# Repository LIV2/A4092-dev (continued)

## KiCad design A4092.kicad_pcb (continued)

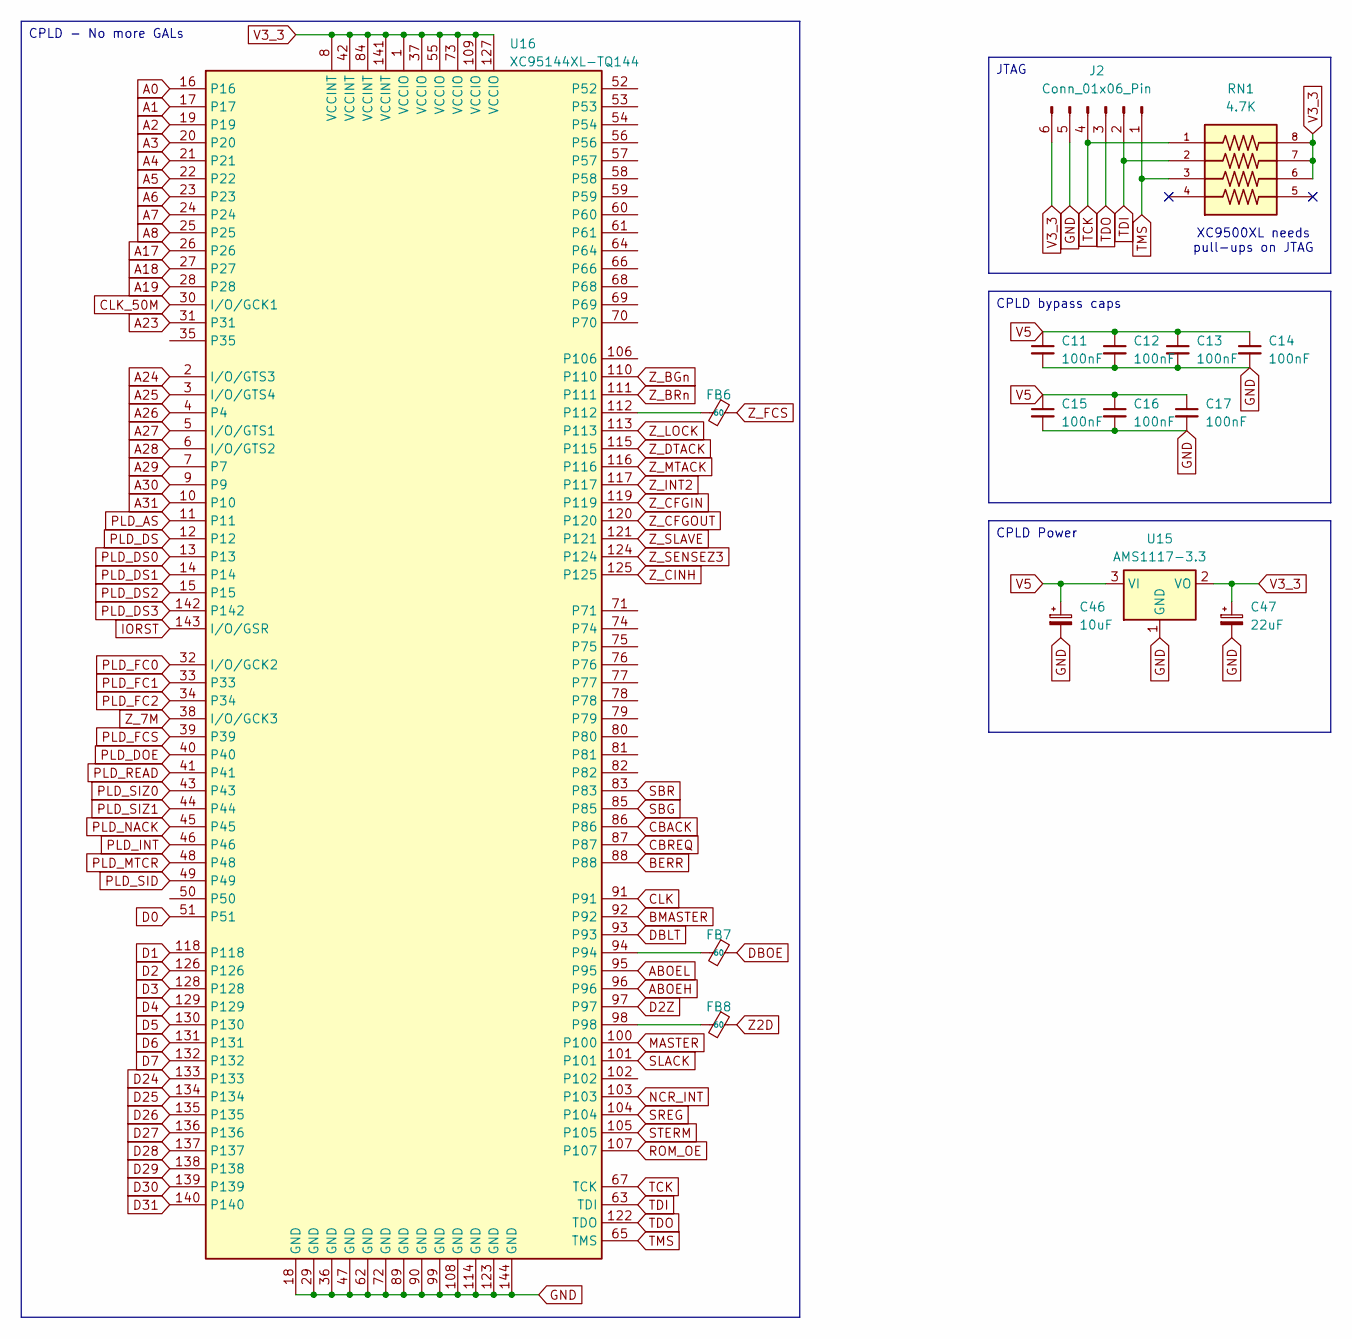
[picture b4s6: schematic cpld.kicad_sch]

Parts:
C11, C12, C13, C14, C15, C16, C17: 100nF; C_0603_1608Metric_Pad1.08x0.95mm_HandSolder
C46: 10uF; CP_Elec_6.3x7.7
C47: 22uF; CP_Elec_6.3x7.7
FB6, FB7, FB8: 60; C_0603_1608Metric_Pad1.08x0.95mm_HandSolder
J2: Conn_01x06_Pin; PinHeader_1x06_P2.54mm_Vertical
RN1: 4.7K; RESCAXS127P508X320X70-8N; PARTREV V.9
U15: AMS1117-3.3; SOT-223-3_TabPin2
U16: XC95144XL-TQ144; 144-TQFP_XIL

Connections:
A0: U16.16; also elsewhere on the board
A1: U16.17; also elsewhere on the board
A2: U16.19; also elsewhere on the board
A3: U16.20; also elsewhere on the board
A4: U16.21; also elsewhere on the board
A5: U16.22; also elsewhere on the board
A6: U16.23; also elsewhere on the board
A7: U16.24; also elsewhere on the board
A8: U16.25; also elsewhere on the board
A17: U16.26; also elsewhere on the board
A18: U16.27; also elsewhere on the board
A19: U16.28; also elsewhere on the board
A23: U16.31; also elsewhere on the board
A24: U16.2 (I/O/GTS3); also elsewhere on the board
A25: U16.3 (I/O/GTS4); also elsewhere on the board
A26: U16.4; also elsewhere on the board
A27: U16.5 (I/O/GTS1); also elsewhere on the board
A28: U16.6 (I/O/GTS2); also elsewhere on the board
A29: U16.7; also elsewhere on the board
A30: U16.9; also elsewhere on the board
A31: U16.10; also elsewhere on the board
ABOEH: U16.96; also elsewhere on the board
ABOEL: U16.95; also elsewhere on the board
BERR: U16.88; also elsewhere on the board
BMASTER: U16.92; also elsewhere on the board
CBACK: U16.86; also elsewhere on the board
CBREQ: U16.87; also elsewhere on the board
CLK: U16.91; also elsewhere on the board
CLK_50M: U16.30 (I/O/GCK1); also elsewhere on the board
D0: U16.51; also elsewhere on the board
D1: U16.118; also elsewhere on the board
D2: U16.126; also elsewhere on the board
D2Z: U16.97; also elsewhere on the board
D3: U16.128; also elsewhere on the board
D4: U16.129; also elsewhere on the board
D5: U16.130; also elsewhere on the board
D6: U16.131; also elsewhere on the board
D7: U16.132; also elsewhere on the board
D24: U16.133; also elsewhere on the board
D25: U16.134; also elsewhere on the board
D26: U16.135; also elsewhere on the board
D27: U16.136; also elsewhere on the board
D28: U16.137; also elsewhere on the board
D29: U16.138; also elsewhere on the board
D30: U16.139; also elsewhere on the board
D31: U16.140; also elsewhere on the board
DBLT: U16.93; also elsewhere on the board
DBOE: FB7.1; also elsewhere on the board
IORST: U16.143 (I/O/GSR); also elsewhere on the board
MASTER: U16.100; also elsewhere on the board
NCR_INT: U16.103; also elsewhere on the board
unnamed: FB7.2, U16.94
unnamed: FB8.2, U16.98
unnamed: FB6.2, U16.112
PLD_AS: U16.11; also elsewhere on the board
PLD_DOE: U16.40; also elsewhere on the board
PLD_DS: U16.12; also elsewhere on the board
PLD_DS0: U16.13; also elsewhere on the board
PLD_DS1: U16.14; also elsewhere on the board
PLD_DS2: U16.15; also elsewhere on the board
PLD_DS3: U16.142; also elsewhere on the board
PLD_FC0: U16.32 (I/O/GCK2); also elsewhere on the board
PLD_FC1: U16.33; also elsewhere on the board
PLD_FC2: U16.34; also elsewhere on the board
PLD_FCS: U16.39; also elsewhere on the board
PLD_INT: U16.46
PLD_MTCR: U16.48; also elsewhere on the board
PLD_NACK: U16.45
PLD_READ: U16.41; also elsewhere on the board
PLD_SID: U16.49; also elsewhere on the board
PLD_SIZ0: U16.43; also elsewhere on the board
PLD_SIZ1: U16.44; also elsewhere on the board
ROM_OE: U16.107; also elsewhere on the board
SBG: U16.85; also elsewhere on the board
SBR: U16.83; also elsewhere on the board
SLACK: U16.101; also elsewhere on the board
SREG: U16.104; also elsewhere on the board
STERM: U16.105; also elsewhere on the board
TCK: J2.4, RN1.1, U16.67 (TCK)
TDI: J2.2, RN1.2, U16.63 (TDI)
TDO: J2.3, U16.122 (TDO)
TMS: J2.1, RN1.3, U16.65 (TMS)
V3_3: C47.1, J2.6, RN1.6, RN1.7, RN1.8, U15.2 (VO), U16.1 (VCCIO), U16.8 (VCCINT), U16.37 (VCCIO), U16.42 (VCCINT), U16.55 (VCCIO), U16.73 (VCCIO), U16.84 (VCCINT), U16.109 (VCCIO), U16.127 (VCCIO), U16.141 (VCCINT)
V5: C11.1, C12.1, C13.1, C14.1, C15.1, C16.1, C17.1, C46.1, U15.3 (VI); also elsewhere on the board
Z2D: FB8.1; also elsewhere on the board
Z_7M: U16.38 (I/O/GCK3); also elsewhere on the board
Z_BGn: U16.110; also elsewhere on the board
Z_BRn: U16.111; also elsewhere on the board
Z_CFGIN: U16.119; also elsewhere on the board
Z_CFGOUT: U16.120; also elsewhere on the board
Z_CINH: U16.125; also elsewhere on the board
Z_DTACK: U16.115; also elsewhere on the board
Z_FCS: FB6.1; also elsewhere on the board
Z_INT2: U16.117; also elsewhere on the board
Z_LOCK: U16.113
Z_MTACK: U16.116; also elsewhere on the board
Z_SENSEZ3: U16.124
Z_SLAVE: U16.121; also elsewhere on the board

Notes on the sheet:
XC9500XL needs pull-ups on JTAG
CPLD - No more GALs
JTAG
CPLD Power
CPLD bypass caps

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
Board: 2 copper layers, 107 parts (0 on the bottom side), 255 nets, no tracks yet.

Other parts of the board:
J8: TO-A3000-LED; PinHeader_1x03_P2.54mm_Vertical
J9: TO-A3000-MB; PinHeader_1x03_P2.54mm_Vertical
RN4, RN5: 1K; BO_CAY16
U6: SN74ABT16543DGGR; DL56

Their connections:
A8: U6.14 (1A8); also elsewhere on the board
A9: U6.13 (1A7); also elsewhere on the board
A10: U6.12 (1A6); also elsewhere on the board
A11: U6.10 (1A5); also elsewhere on the board
A12: U6.9 (1A4); also elsewhere on the board
A13: U6.8 (1A3); also elsewhere on the board
A14: U6.6 (1A2); also elsewhere on the board
A15: U6.5 (1A1); also elsewhere on the board
ABOEH: U6.56 (*1OEBA); also elsewhere on the board
BMASTER: U6.54 (*1CEBA); also elsewhere on the board
DIP_EXT_TERM: RN5.3; also elsewhere on the board
DIP_LONG_SPINUP: RN5.1; also elsewhere on the board
DIP_SCSI_ADDR0: RN4.1; also elsewhere on the board
DIP_SCSI_ADDR1: RN4.2; also elsewhere on the board
DIP_SCSI_ADDR2: RN4.3; also elsewhere on the board
DIP_SCSI_FAST: RN4.4; also elsewhere on the board
DIP_SCSI_LUNS: RN5.4; also elsewhere on the board
DIP_SYNCH_MODE: RN5.2; also elsewhere on the board
IORST: U6.1 (*1OEAB); also elsewhere on the board
LED3KPWR: J8.3, J9.3
LEDR: J8.2, J9.2; also elsewhere on the board
MASTER: U6.3 (*1CEAB); also elsewhere on the board
PLD_FCS: U6.55 (*1LEBA); also elsewhere on the board
V5: J8.1, J9.1, RN4.5, RN4.6, RN4.7, RN4.8, RN5.5, RN5.6, RN5.7, RN5.8, U6.7 (VCC), U6.22 (VCC), U6.35 (VCC), U6.50 (VCC); also elsewhere on the board
Z_A8D0: U6.43 (1B8); also elsewhere on the board
Z_A9D1: U6.44 (1B7); also elsewhere on the board
Z_A10D2: U6.45 (1B6); also elsewhere on the board
Z_A11D3: U6.47 (1B5); also elsewhere on the board
Z_A12D4: U6.48 (1B4); also elsewhere on the board
Z_A13D5: U6.49 (1B3); also elsewhere on the board
Z_A14D6: U6.51 (1B2); also elsewhere on the board
Z_A15D7: U6.52 (1B1); also elsewhere on the board

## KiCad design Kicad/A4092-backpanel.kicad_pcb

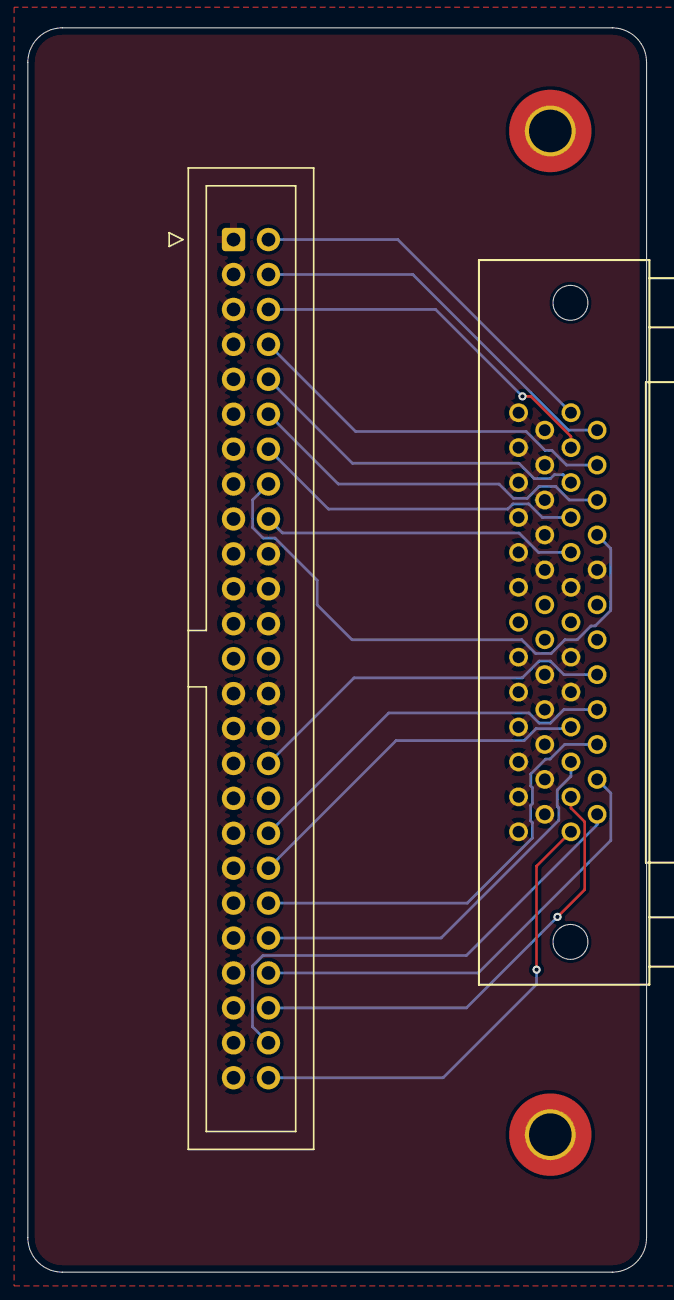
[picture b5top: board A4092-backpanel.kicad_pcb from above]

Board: 2 copper layers, 45.0 x 90.5 mm, 4 parts (0 on the bottom side), 20 nets.

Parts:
H1, H2: MOUNT_HOLE; MOUNT_HOLE_M3
J1: Conn_02x25_Odd_Even; IDC-Header_2x25_P2.54mm_Vertical
J2: 5787170-5; CONN_5787170-5_TYC

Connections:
GND: J1.1, J1.3, J1.5, J1.7, J1.9, J1.11, J1.13, J1.15, J1.17, J1.19, J1.20, J1.21, J1.22, J1.23, J1.24, J1.27, J1.28, J1.29, J1.30, J1.31, J1.33, J1.35, J1.37, J1.39, J1.41, J1.43, J1.45, J1.47, J1.49, J2.1, J2.2, J2.3, J2.4, J2.5, J2.6, J2.7, J2.8, J2.9, J2.10, J2.11, J2.15, J2.16, J2.17, J2.18, J2.19, J2.20, J2.21, J2.22, J2.23, J2.24, J2.25, J2.35, J2.36, J2.40, J2.42
SCDAT0: J1.2, J2.26
SCDAT1: J1.4, J2.27
SCDAT2: J1.6, J2.28
SCDAT3: J1.8, J2.29
SCDAT4: J1.10, J2.30
SCDAT5: J1.12, J2.31
SCDAT6: J1.14, J2.32
SCDAT7: J1.16, J2.33
SCDATP: J1.18, J2.34
SCSI_TERMPWR: J1.26, J2.38
SCTRL_ACK: J1.38, J2.44
SCTRL_ATN: J1.32, J2.41
SCTRL_BSY: J1.36, J2.43
SCTRL_CD: J1.46, J2.48
SCTRL_IO: J1.50, J2.50
SCTRL_MSG: J1.42, J2.46
SCTRL_REQ: J1.48, J2.49
SCTRL_RST: J1.40, J2.45
SCTRL_SEL: J1.44, J2.47

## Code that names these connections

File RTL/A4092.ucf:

# P1 - VCCIO
NET "D<15>"       LOC = "P2";
NET "ROM_CE_n"    LOC = "P3";
NET "ROM_WE_n"    LOC = "P4";
NET "ROM_OE_n"    LOC = "P5";
NET "A<0>"        LOC = "P6";
NET "A<1>"        LOC = "P7";
# P8 - VCCINT
NET "A<2>"        LOC = "P9";
NET "A<3>"        LOC = "P10";
NET "A<4>"        LOC = "P11";
NET "A<5>"        LOC = "P12";
NET "A<6>"        LOC = "P13";
NET "A<7>"        LOC = "P14";
NET "A<8>"        LOC = "P15";
NET "A<9>"        LOC = "P16";
NET "A<10>"       LOC = "P17";
# P18 - GND
NET "A<11>"       LOC = "P19";
NET "A<12>"       LOC = "P20";
NET "A<13>"       LOC = "P21";
NET "A<14>"       LOC = "P22";
NET "A<15>"       LOC = "P23";
NET "A<16>"       LOC = "P24";
NET "A<17>"       LOC = "P25";
NET "A<18>"       LOC = "P26";
NET "A<19>"       LOC = "P27";
NET "A<20>"       LOC = "P28";
# P29 - GND
NET "CLK_50M"     LOC = "P30";
NET "CLK_50M" TNM_NET = "CLK_50M";
TIMESPEC "TS_CLK_50M" = PERIOD "CLK_50M" 20 ns HIGH 50%;
NET "SCSI_AS_n"   LOC = "P31";
NET "SCSI_DS_n"   LOC = "P32";
NET "SPI_CLK"     LOC = "P33";
NET "SPI_MOSI"    LOC = "P34";
NET "SPI_MISO"    LOC = "P35";
# P36 - GND
# P37 - VCCIO
NET "C7M"        LOC = "P38";
NET "C7M" TNM_NET = "C7M";
TIMESPEC "TS_C7M" = PERIOD "C7M" 139.68 ns HIGH 50%;
NET "SPI_CS_n"    LOC = "P39";
NET "DOE"         LOC = "P40";
NET "READ"        LOC = "P41";
# P42 - VCCINT
NET "SIZ<0>"      LOC = "P43";
NET "SIZ<1>"      LOC = "P44";
# P45 - NC
# P46 - NC
# P47 - GND
NET "MTCR_n"      LOC = "P48";
NET "SID_n"       LOC = "P49";
NET "DIP_EXT_TERM" LOC = "P50";
# P51 - NC
# P52 - NC
# P53 - NC
# P54 - NC
# P55 - VCCIO
# P56 - NC
# P57 - NC
# P58 - NC
NET "A<23>"       LOC = "P59";
NET "A<24>"       LOC = "P60";
NET "A<25>"       LOC = "P61";
# P62 - GND
# P63 - TDI
NET "A<26>"       LOC = "P64";
# P65 - TMS
NET "A<27>"       LOC = "P66";
# P67 - TCK
NET "A<28>"       LOC = "P68";
NET "A<29>"       LOC = "P69";
NET "A<30>"       LOC = "P70";
NET "A<31>"       LOC = "P71";
# P72 - GND
# P73 - VCCIO
NET "FCS"         LOC = "P74";
NET "FC<0>"       LOC = "P75";
NET "FC<1>"       LOC = "P76";
NET "FC<2>"       LOC = "P77";
NET "DS_n<0>"     LOC = "P78";
NET "DS_n<1>"     LOC = "P79";
NET "DS_n<2>"     LOC = "P80";
NET "DS_n<3>"     LOC = "P81";
NET "D<14>"       LOC = "P82";
NET "SBR_n"       LOC = "P83";
# P84 - VCCINT
NET "SBG_n"       LOC = "P85";
NET "CBACK_n"     LOC = "P86";
NET "CBREQ_n"     LOC = "P87";
NET "BERR_n"      LOC = "P88";
# P89 - GND
# P90 - GND
NET "CLK"         LOC = "P91";
NET "BMASTER"     LOC = "P92";
NET "DBLT"        LOC = "P93";
NET "DBOE_n"      LOC = "P94";
NET "ABOEL_n"     LOC = "P95";
NET "ABOEH_n"     LOC = "P96";
NET "D2Z_n"       LOC = "P97";
NET "Z2D_n"       LOC = "P98";
# P99 - GND
NET "MASTER_n"    LOC = "P100";
NET "SLACK_n"     LOC = "P101";
NET "D<13>"       LOC = "P102";
NET "SINT_n"      LOC = "P103";
NET "SCSI_SREG_n" LOC = "P104";
NET "SCSI_STERM_n" LOC = "P105";
NET "INT2_n"      LOC = "P106";
NET "D<12>"       LOC = "P107";
# P108 - GND
# P109 - VCCIO
NET "BGn"         LOC = "P110";
NET "BRn"         LOC = "P111";
NET "Z_FCS_n"     LOC = "P112";
NET "Z_LOCK"      LOC = "P113";
# P114 - GND
NET "DTACK_n"     LOC = "P115";
NET "MTACK_n"     LOC = "P116";
NET "CINH_n"      LOC = "P117";
NET "SENSEZ3_n"   LOC = "P118";
NET "CFGIN_n"     LOC = "P119";
NET "CFGOUT_n"    LOC = "P120";
NET "SLAVE_n"     LOC = "P121";
# P122 - TDO
# P123 - GND
NET "D<0>"        LOC = "P124";
NET "D<1>"        LOC = "P125";
NET "D<2>"        LOC = "P126";
# P127 - VCCIO
NET "D<3>"        LOC = "P128";
NET "D<4>"        LOC = "P129";
NET "D<5>"        LOC = "P130";
NET "D<6>"        LOC = "P131";
NET "D<7>"        LOC = "P132";
NET "D<24>"       LOC = "P133";
NET "D<25>"       LOC = "P134";
NET "D<26>"       LOC = "P135";
NET "D<27>"       LOC = "P136";
NET "D<28>"       LOC = "P137";
NET "D<29>"       LOC = "P138";
NET "D<30>"       LOC = "P139";
NET "D<31>"       LOC = "P140";
# P141 - VCCINT
# P142 - NC
NET "IORST_n"     LOC = "P143";
NET "IORST_n" TIG;  # Ignore timing on async reset
# P144 - GND

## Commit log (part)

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2025-03-05 Empty KiCad project
2025-03-05 Add hierarchy
2025-03-11 Start populating Zorro III
2025-03-12 Add symbol for NCR53c710
2025-03-12 Add 39SF010 symbol
2025-03-12 Remove bak file and add footprint/symbol tables
2025-03-12 Place CPLD, NCR and last 543 (Latched Trabceiver)
2025-03-16 Update design
2025-03-23 Add external SCSI connector
2025-03-24 Redraw footprints, finish Termination/Connectors
2025-03-26 More work. Getting there.
2025-03-29 Update footprints
2025-03-29 Latest updates
2025-03-29 Finished first pass at new schematics
2025-03-30 Update RN footprint to CAY16_102J4LF
    - Rename RNs from R to RN.
    - Fix U5 footprint
    - Rename pages to be consecutive numbers
2025-03-30 Connect VCCINT on CPLD, add GND and V5 to power symbols
2025-03-30 Switch to 74ABT16543
2025-03-30 Remove ABT TODO
2025-03-30 Incorporate Feedback from LIV2
    - Move CLK, CLKI, Z_7M to GCLK1, GCLK2, GCLK3
    as they are connected to all macro cells.
    - OE1 and GCLR on the 1508 are input only, move FC0/FC1 there.
    Also found two duplicate signals on the ATF1508, consolidated them.
    This leaves us with 8 free I/Os at the moment.
2025-03-30 Add link to datasheet to cpld
2025-03-30 Drop 74ABT74
    The 74ABT74 is only used as a divider to create 25MHz from the 50MHz clock, and
    it can be removed. Instead, the 50MHz are directly brought to the ATF1508. CLK
    will be used as an output, not an input, so move away from GCLK pin. CLKI is no
    longer needed on a pin as it doesn't connect to anything anymore.
2025-03-30 Move IORST to Reset / GCLR Pin
2025-03-30 Free up some pins and add an LED
2025-04-01 Move to XC95144XL
    and other changes related to that.
2025-04-02 Add .gitignore
2025-04-02 1. Placement looks feasible on 1 layer. Pending routing confirmation. 2. pages 1-2 placed. 3. components outside the outline are looking for a new home.
2025-04-02 Add skeleton to include Gerbers, BOM files, RTL etc
2025-04-03 Rotaded J1 by 180 degree and re-arrange components close to the controller
2025-04-10 Routed several nets
2025-04-10 Start adding pin descriptions to A4092 RTL
2025-04-11 Remove lock files and ignore them
2025-04-11 Routing in progress
2025-04-11 CPLD bypass caps need to be on the 3.3V rail, not 5V
2025-04-11 Remove large Molex power connector
2025-04-11 Resync the PCB from Schematics, add some 3d models
2025-04-11 Update Kicad project file
2025-04-12 Fixed SCSI connector footprint. Added 3d models for all parts.
2025-04-12 Fix Xilinx 3d model in footprint
2025-04-12 Fix HS_GND connection on pin2 of the scsi terminators
2025-04-13 Ignore backups
2025-04-13 Add Picture
2025-04-13 SW1 and U10 breakout
2025-04-15 Fix 74FCT16543 and CAY16_102J4LF footprints
2025-04-16 SCSI Controller breakout
2025-04-18 CPLD fixes
    * Terminate unused CPLD connections with NC
    * Move D0 to pin 117 to line up with the other databus pins
2025-04-18 Rename all Uxx parts from U1 to U13 for consistency
2025-04-19 Fix up some silkscreen
2025-04-19 Undo silkscreen changes
2025-04-19 Move D0/D1 (again) and remove PLD_INT
2025-04-19 routing progress
2025-04-19 Import netlist from commit: Move D0/D1 (again) and remove PLD_INT
2025-04-19 Clean up CPLD signals / prepare for rotation
2025-04-20 Fix Zorro III symbol
2025-04-20 ROM_WE Single net Issue #3
    Connect ROM_WE to CPLD. Also connect ROM_CE.
2025-04-20 Fix Z_LOCK in zorro3 schematics
2025-04-20 CPLD Routing
2025-04-20 Your commit message
2025-04-20 PLD_NACK is only a CPLD internal signal
2025-04-20 This should be PLD_DS0, not PLD_DS1
2025-04-20 CPLD pin net swap (issue #7)
    • PLD_FC0-FC2 nets move from Pin 2-4 to 75-77
    • PLD_DS0-DS2 nets move from Pin 33-35 to 78-80
    • ROM_WE net move from Pin 102 to 5
    • ROM_OE net move from Pin 107 to 4
    Additionally moved ROM_CE to P3 and PLD_DS3 to P81
2025-04-20 Update PCB from schematics
2025-04-20 Add Kicad/A4092.kicad_prl to .gitignore
2025-04-20 Clean up top level
2025-04-20 Fix various errors from issue #1
2025-04-20 routin gin progress
2025-04-20 Update from schematics
2025-04-20 Stop tracking A4092.kicad_prl
2025-04-20 Add footprint to pull down of ROM_CE
2025-04-20 Add pulldown of ROM_CE to PCB
2025-04-20 Routing
2025-04-21 Update image
2025-04-22 Move transceivers north
2025-04-22 more routing
2025-04-23 Fix issues #12 and #13
    Z_BEER and SCSI_BUSY were not connected correctly (single net pins)
2025-04-23 Implement autoconfig (courtesy Matt Harlum)
2025-04-24 Feedback impleted for: [200~SCSI_TERMPWR traces should be 0.3mm min~
2025-04-24 Feedback implemented:Make sure card guides don't hit components on the left side
2025-04-26 Move HPDB50 connector to back panel
2025-04-29 General routing
2025-05-03 Rename majority of bypass capacitors to match their Uxx
    i.e. U4 will have C4A, C4B, C4C, C4D
2025-05-03 Revert: Rename majority of bypass capacitors to match their Uxx
2025-05-05 Replace C47 and C46 with Tantalum capacitors
2025-05-05 Add more bypass caps
2025-05-05 Rename capacitors
2025-05-06 Fix up silkscreen across the board
2025-05-06 RTL: Add ROM access
2025-05-06 RTL: Add SID (SCSI ID jumper) access
2025-05-06 RTL: Add intreg access
2025-05-06 RTL: INTVEC support
2025-05-06 Add memory map overview comment to top level module
2025-05-06 add actual scsi access and buffer control
2025-05-06 RTL: Add DBLT
2025-05-07 Add INT2 handling
2025-05-07 Add more remaining signals
2025-05-07 Zorro Master Arbiter
2025-05-07 Add clocks, replace 74F74
2025-05-07 Fix up molex connector
2025-05-07 Fix pin mapping
2025-05-09 Update termination capacitors to tantalum
    and clean up bypass caps in schematic
2025-05-09 Add two missing bulk power caps from old schematics
2025-05-11 Some compilation fixes
2025-05-11 More compile fixes.
2025-05-12 Try to fix up pin naming
2025-05-12 Connect SC0 from 53c710 to CPLD
    This will let us implement the "False DMA Request Bugfix"
2025-05-12 Use Z_LOCK/A1 for intreg
2025-05-12 Zorro Master Arbiter needs Z_FCS
2025-05-15 HD50 conn routing
2025-05-15 Kicad: Pin swaps on RN10 and RN16
    Fixes issue #1 and issue #2
2025-05-16 SW1 routing
2025-05-17 Signal routing
2025-05-17 DRCs checks
2025-05-17 bypass caps routing
2025-05-18 V3_3 routing
2025-05-18 PWR routing
2025-05-18 Remove a rogue NC
2025-05-18 Connect DIP_EXT_TERM to CPLD
2025-05-18 Add option to move SID into CPLD / flash entirely
2025-05-19 Add correct footprints for DIP resistors
    And start adding LCSC part numbers
2025-05-19 GND connections
2025-05-20 Add more LCSC parts and mark some parts DNP
2025-05-20 Update PCB from schematic
2025-05-20 RN15 pin swap
    As requested in issue #7
2025-05-20 Pin swap on RN15 the right way
2025-05-20 Update PCB from schematic, routing
2025-05-20 Add remaining part numbers, remove C20, C30, C31
2025-05-21 Fix LCSC parts issues
2025-05-21 Update PCB file
2025-05-21 Use APAQ Tech 250AVHA470M0606 not AVEA
2025-05-21 Update SCSI connector
2025-05-23 Improve Zorro III connector and round off PCB outline
2025-05-23 Update footprint graphics
    Unify using a dot rather than asterisk for pin 1
    Remove pin 1 designator for ferrites
2025-05-23 Clean up schematics
2025-05-24 Minor trace and silkscreen fixes
2025-05-26 V5 routing in progress
2025-05-26 routing is completed
2025-05-26 Add fiducials and clean up schematics
2025-05-26 Update PCB image
2025-05-27 GND vias
2025-05-27 Add SPI flash option and move flash to its own page
2025-05-27 Hook up Flash page
2025-05-27 Recreate PCB from schematics
    Changed footprints to sync cleanly on the Mac
2025-05-28 Add D[12..15] and A[9..16,20] to CPLD
2025-05-28 Fix 3V3 -> V3_3
2025-05-28 Review fixes on scsi2 page
    * R11 is 22 Ohm not 120 in the original schematics
    * FETCH# is NC in the original, not V5
2025-05-28 Imported latest netlist
2025-05-28 Add bypass cap for Berg connector
2025-05-28 Add GAL source code for reference
2025-05-28 Add Zorro 3 DMA master
2025-05-29 board cleanup
2025-05-29 Imported netlist
2025-05-29 Restructure directories, Add Terminator designs
2025-05-29 Move A4092 main PCB to subdirectory
    - Move current main design to A4092
    - Add fp-lib-table and sym-lib-table with correct paths to
    each sub directory
2025-05-30 RTL: Add additional data and address lines
    and fix address map
2025-05-30 RTL: Add additional address, data and spi signals
2025-06-01 A4092 text Top cutout
2025-06-01 Fix 3d image path in footprints
2025-06-01 Update RTL
2025-06-01 Update JLCPCB part numbers
    Move to available and, if possible, basic parts
2025-06-01 Removed fiducial copper and copper sliver rule
2025-06-05 Fix Data Bus output
2025-06-05 Drop u304.txt
2025-06-05 Remove ^Z from GAL source
2025-06-06 Update PCB from Schematics, new image
2025-06-06 Add SN74ABT16543DGGR symbol / footprint
2025-06-06 Update to use new footprint for U1,2,3,4
2025-06-06 U1-4 routing completed
2025-06-06 Update PCB
2025-06-07 Add Gerbers
2025-06-07 RTL: Drop double assignment of DOE and DS_n
2025-06-07 RTL: Fix signal naming and hook up right bits of DIP
2025-06-08 Fix address mapping
2025-06-08 RTL: Address matching for intreg
    Make address matching for intreg the same as for everything else,
    using bits 23-17
2025-06-08 Update LT1118-2.85 based terminator
2025-06-09 Update DEV version of the terminator
    with switch for experimenting w/ mosfet
2025-06-09 Finish DS2107 terminator
2025-06-09 Fix up capacitor array footprint
    家裡創 did not like the digikey footprint.
2025-06-09 Add rotations for all parts
2025-06-10 Update Backpanel for smaller footprint
2025-06-12 Initial attempt at a4092flash, based on LIV2's lideflash
2025-06-12 Adjust flash.c for A4092 flash memory mapping
2025-06-13 Fix 3d model path
2025-06-13 Fix 3d model for TSSOP-48
2025-06-13 Allow bridged solder mask for Zorro3 connector
2025-06-13 Remove spaces from JLCPCB part numbers
2025-06-14 Fix up Makefile / kibot calls
2025-06-15 Update kibot config
2025-06-29 buffer control was way off
2025-06-30 Move regions to top level
2025-06-30 buffer_control: Plumb through all buffer enables
    When an input pin on a BiCMOS logic chip like the SN74ABT543 is left floating
    (unconnected), its voltage can drift into an indeterminate state, somewhere
    between a valid logic HIGH and a valid logic LOW.
    In this intermediate state, both the internal pull-up and pull-down transistors
    inside the chip's input buffer can turn on simultaneously. This creates a
    low-impedance path directly from the power supply (Vcc) to ground (GND). This
2025-07-01 Move memory map handling into top.v
    - Rename Z_7M to C7M
    - Rename MYBBUS to MYBUS_n as it is active low
    - Don't pass ADDR[] into modules if not needed
    (intreg still missing)
    - Fix SBG_n in zorro arbiter
2025-07-01 Fix RCHNG in zorro arbiter
    and add dummy spi module
2025-07-02 Define MTACK_n and CBACK_n
2025-07-02 INT2_n is shared so it should be 0 or Z
2025-07-02 factor out scsi slave module
    - stub out spi module
    - top: A[] is now inout
    - top: CLK and MASTER_n are wires
    - top: SIZ is an output to the SCSI chip
    - straighten zorro arbiter
2025-07-02 Fix signal names for scsi slave interface
2025-07-03 MASTER_n is an input in our design
2025-07-10 a4092flash: Fix detection and verification
2025-07-12 intreg: NCR_INT is low active,
2025-07-12 Autoconfig update from Dorken
    - We need 8 bits for the BAR portion of the address as our address
    space is only 16MB, not 256.
    - The A4092 is using 16543 for multiplexing the data and address bus,
    so we can assume that A[] and D[] are valid when we read them, no
    need to look at z3_state.
    - Disable Automatic sizing by the OS, this only works with memory cards
2025-07-12 FCS is high active and Z_FCS_n is low active
    Found by Dorken
2025-07-12 Autoconfig update part 2
2025-07-12 Simplify address bus logic
    We have 2 74ABT16543 to buffer our bus access. So we
    can drop logic around doing the same in the CPLD. (Dorken)
2025-07-12 No need for DTACK, handled by buffer_control.v
2025-07-12 Zorro protocol
2025-07-12 Add xise file
2025-07-12 Fix verification code in a4092flash
2025-07-13 Clean up rom_access.v
2025-07-13 Fixup address decodes
    *_region was matching when slave_cycle was true but without checking that the base address matched - this would cause these regions to match when other Z3 boards are being accessed
